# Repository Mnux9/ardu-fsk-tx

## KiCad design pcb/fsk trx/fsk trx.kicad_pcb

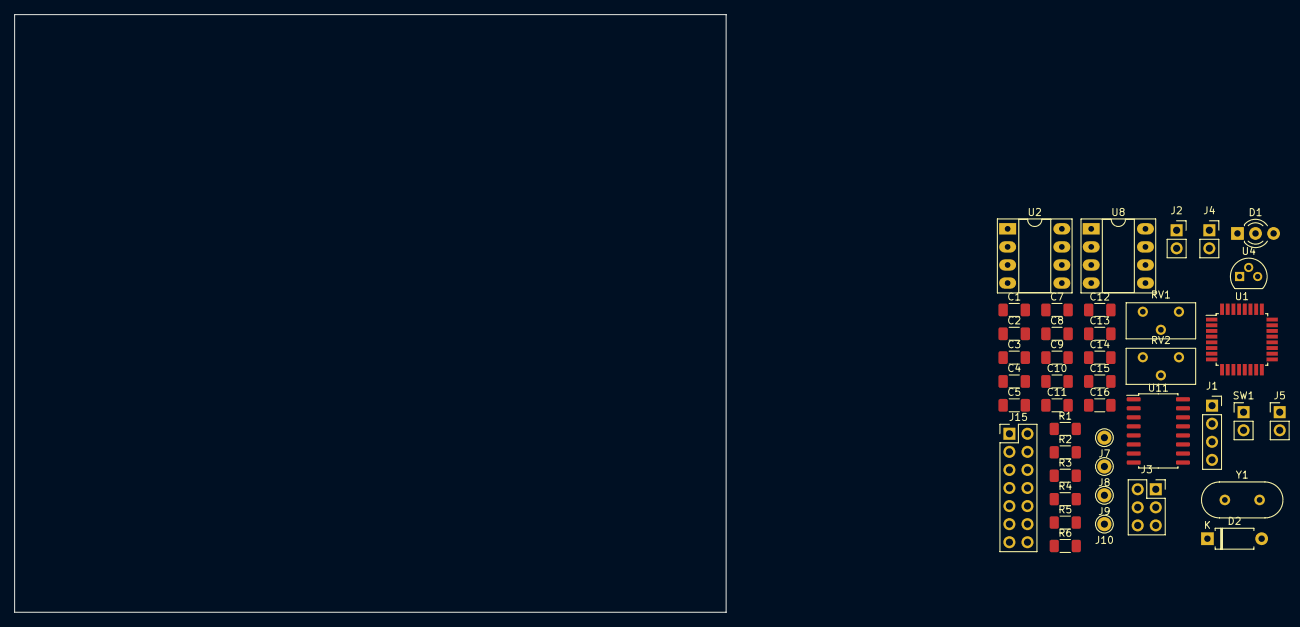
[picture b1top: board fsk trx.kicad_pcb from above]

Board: 2 copper layers, 100.0 x 84.0 mm, 42 parts (0 on the bottom side), 35 nets, no tracks yet.

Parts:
C1, C2, C3, C4, C5, C7, C9, C10, C11, C12, C13, C14, C15, C16: C; C_1206_3216Metric_Pad1.33x1.80mm_HandSolder
C8: C_Polarized; C_1206_3216Metric_Pad1.33x1.80mm_HandSolder
D1: LED_Dual_AKA; LED_D3.0mm-3
D2: D; D_A-405_P7.62mm_Horizontal
J1: Conn_01x04_Male; PinSocket_1x04_P2.54mm_Vertical
J2, J4: Conn_01x02_Male; PinSocket_1x02_P2.54mm_Vertical
J3: Conn_02x03_Odd_Even; PinSocket_2x03_P2.54mm_Vertical
J5: Conn_01x02_Male; PinHeader_1x02_P2.54mm_Vertical
J7, J8, J9, J10: Conn_01x01_Male; Pin_D1.0mm_L10.0mm
J15: Conn_02x07_Counter_Clockwise; PinHeader_2x07_P2.54mm_Vertical
R1, R2, R3, R4, R5, R6: R; R_1206_3216Metric_Pad1.30x1.75mm_HandSolder
RV1, RV2: R_Potentiometer; Potentiometer_Bourns_3296Y_Vertical
SW1: SW_Push; PinHeader_1x02_P2.54mm_Vertical
U1: ATmega328PB-A; TQFP-32_7x7mm_P0.8mm
U2: LM393; DIP-8_W7.62mm_Socket_LongPads
U4: L7805; TO-92L
U8: NE5534; DIP-8_W7.62mm_Socket_LongPads
U11: PCF8574; SO-16_5.3x10.2mm_P1.27mm
Y1: Crystal; Crystal_HC49-4H_Vertical

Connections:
+5V: C4.1, C9.2, C13.2, C15.2, C16.2, J3.5, J15.2, R1.1, R6.2, RV2.3, U1.4 (VCC), U2.8 (V+), U4.3 (OUT), U11.16 (VDD)
A IN: J2.1, U2.2 (-)
BCK LIGHT: J5.1, U1.32 (PD2)
GND: C1.2, C2.2, C3.2, C4.2, C8.2, C9.1, C10.1, C11.1, C12.2, C13.1, C14.1, C15.1, C16.1, D1.2 (K), J1.4, J2.2, J3.1, J4.2, J5.2, J9.1, J10.1, J15.1, R3.1, RV2.1, SW1.1, U1.5 (GND), U1.21 (GND), U2.3 (+), U2.4 (V-), U2.6 (-), U4.2 (GND), U11.8 (VSS)
GND2: J7.1, J8.1
LCD_3(VO): J15.3, RV2.2
LCD_4(RS): J15.4, U11.4 (P0)
LCD_5(RW): J15.5, U11.5 (P1)
LCD_6(CS): J15.6, U11.6 (P2)
LCD_11(DB4): J15.11, U11.9 (P4)
LCD_12(DB5): J15.12, U11.10 (P5)
LCD_13(DB6): J15.13, U11.11 (P6)
LCD_14(D7): J15.14, U11.12 (P7)
MISO: J3.6, U1.16 (PB4)
MOSI: J3.3, U1.15 (PB3)
unnamed: C14.2, R6.1
unnamed: D1.1 (A1), R5.2
unnamed: D1.3 (A2), R4.2
unnamed: D2.2 (A), J4.1
unnamed: R2.1, RV1.3
unnamed: R3.2, RV1.1
unnamed: R1.2, U1.12 (PB0), U2.1
unnamed: R4.1, U1.2 (PD4)
unnamed: R5.1, U1.9 (PD5)
unnamed: SW1.2, U1.11 (PD7)
unnamed: C1.1, U1.7 (XTAL1/PB6), Y1.2
unnamed: C2.1, U1.8 (XTAL2/PB7), Y1.1
RST: J1.1, U1.29 (~RESET/PC6)
SCK: J3.4, U1.17 (PB5)
SCL: C12.1, U1.28 (PC5), U11.14 (SCL)
SDA: C11.2, U1.27 (PC4), U11.15 (SDA)
UART RX: J1.2, U1.30 (PD0)
UART TX: J1.3, U1.31 (PD1)
VIN: C3.1, C8.1, D2.1 (K), R2.2, U4.1 (IN)
VIN Mesure: C10.2, RV1.2, U1.23 (PC0)

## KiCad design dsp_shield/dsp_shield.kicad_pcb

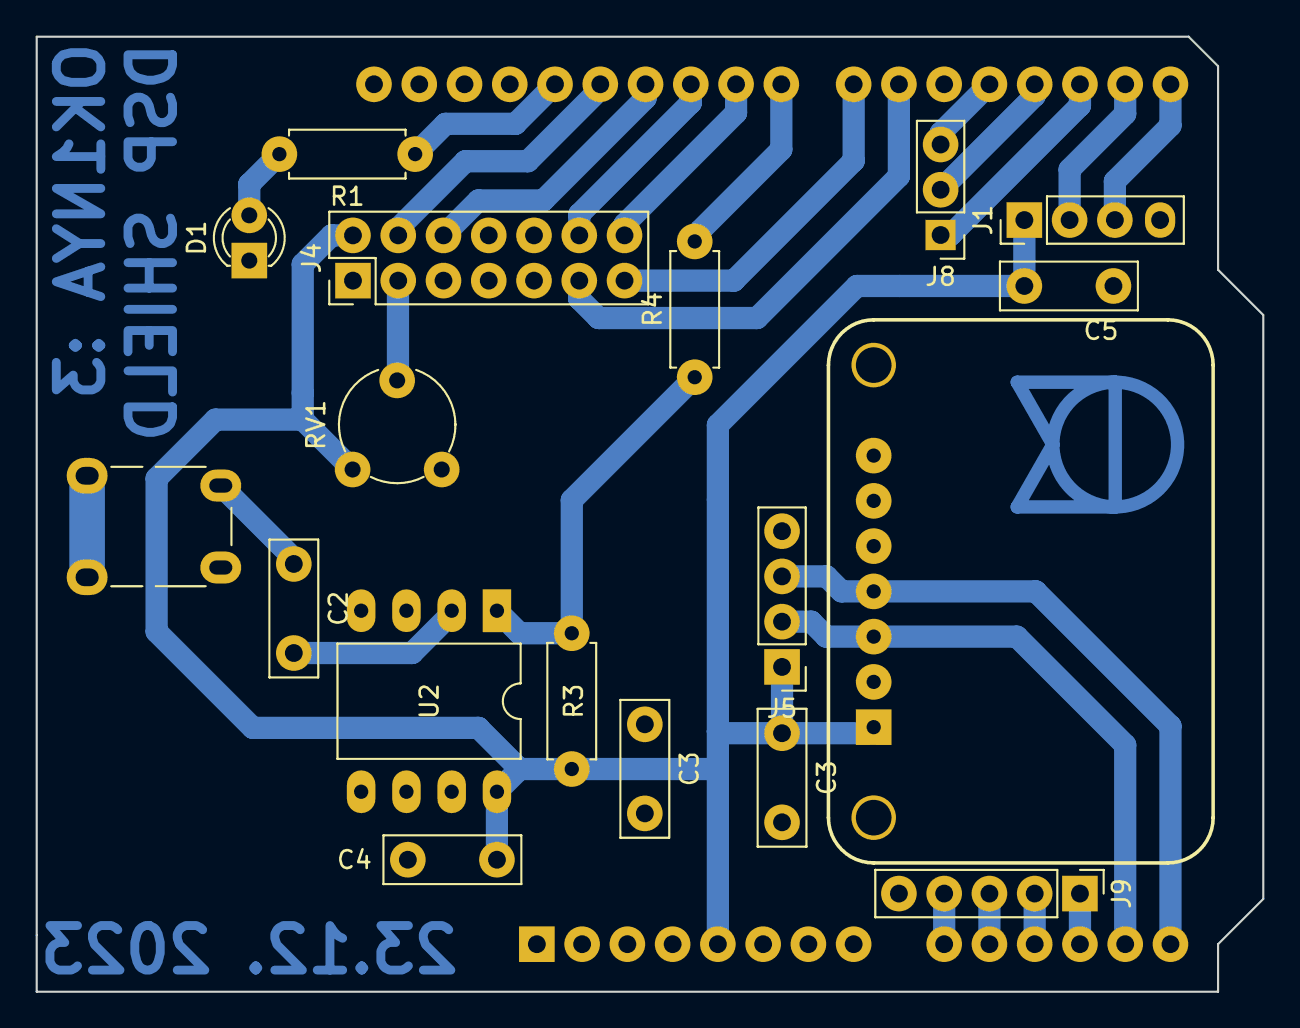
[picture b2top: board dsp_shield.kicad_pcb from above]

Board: 2 copper layers, 68.8 x 53.6 mm, 19 parts (0 on the bottom side), 25 nets.

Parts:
A1: Arduino_UNO_R3; Arduino_UNO
C2, C3, C3#2, C4, C5: C; C_Disc_D7.5mm_W2.5mm_P5.00mm
D1: LED; LED_D3.0mm_Clear
J1, J5: Conn_01x04_Pin; PinHeader_1x04_P2.54mm_Vertical
J2: AudioJack3; Jack_3.5mm_Lumberg_1503_07_Horizontal
J3: Conn_01x07_Socket; si5351a_Module
J4: Conn_02x07_Odd_Even; PinHeader_2x07_P2.54mm_Vertical
J8: Conn_01x03_Pin; PinHeader_1x03_P2.54mm_Vertical
J9: Conn_01x05_Pin; PinHeader_1x05_P2.54mm_Vertical
R1, R3, R4: R; R_Axial_DIN0207_L6.3mm_D2.5mm_P7.62mm_Horizontal
RV1: R_Potentiometer; Potentiometer_Piher_PT-6-V_Vertical
U2: LM393; DIP-8_W10.16mm_LongPads

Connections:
GND: A1.6 (GND), A1.7 (GND), A1.29 (GND), C3.2, C3#2.1, C3#2.2, C4.2, C5.2, D1.1 (K), J1.4, J2.S, J3.2, J4.1, J4.5, J5.4, J9.5, RV1.1, U2.3 (+), U2.4 (V-), U2.6 (-)
LCD_D4: A1.21 (D6), J4.11
LCD_D5: A1.25 (D10), J4.12
LCD_D6: A1.22 (D7), J4.13
LCD_D7: A1.24 (D9), J4.14
LCD_E: A1.26 (D11), J4.6
LCD_RS: A1.27 (D12), J4.4
LCD_V0: J4.3, RV1.2
LCD_VDD: A1.5 (+5V), C3.1, C4.1, C5.1, J1.1, J3.1, J4.2, J5.1, R3.1, RV1.3, U2.8 (V+)
unnamed: A1.9 (A0), J9.4
unnamed: A1.10 (A1), J9.3
unnamed: A1.11 (A2), J9.2
unnamed: A1.12 (A3), J9.1
unnamed: A1.17 (D2), J8.1
unnamed: A1.18 (D3), J8.2
unnamed: A1.19 (D4), J8.3
unnamed: A1.23 (D8), R4.2
unnamed: A1.28 (D13), R1.1
unnamed: C2.1, J2.R
unnamed: R3.2, R4.1, U2.1
unnamed: C2.2, U2.2 (-)
SCL: A1.14 (SCL/A5), J3.4, J5.3
SDA: A1.13 (SDA/A4), J3.3, J5.2
UART_RX: A1.15 (D0/RX), J1.3
UART_TX: A1.16 (D1/TX), J1.2
